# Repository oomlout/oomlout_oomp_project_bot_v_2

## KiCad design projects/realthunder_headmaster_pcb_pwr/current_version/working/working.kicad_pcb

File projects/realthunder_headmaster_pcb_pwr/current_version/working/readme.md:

# headmaster_pcb
 
## summary 
* id: realthunder_headmaster_pcb_pwr
* user: realthunder
* name: headmaster_pcb
* board: pwr
* repo: https://github.com/realthunder/headmaster_pcb
* src_file_repo_kicad_pcb: subs/body/pwr/pwr.kicad_pcb
* src_file_repo_kicad_pcb_link: https://github.com/realthunder/headmaster_pcb/tree/master/subs/body/pwr/pwr.kicad_pcb

* src_file_repo_sch: subs/body/pwr/pwr.sch
* src_file_repo_sch_link: https://github.com/realthunder/headmaster_pcb/tree/master/subs/body/pwr/pwr.sch
* full details link: https://github.com/oomlout/oomlout_oomp_project_bot_v_2/tree/main/projects/realthunder_headmaster_pcb_pwr/current_version/working

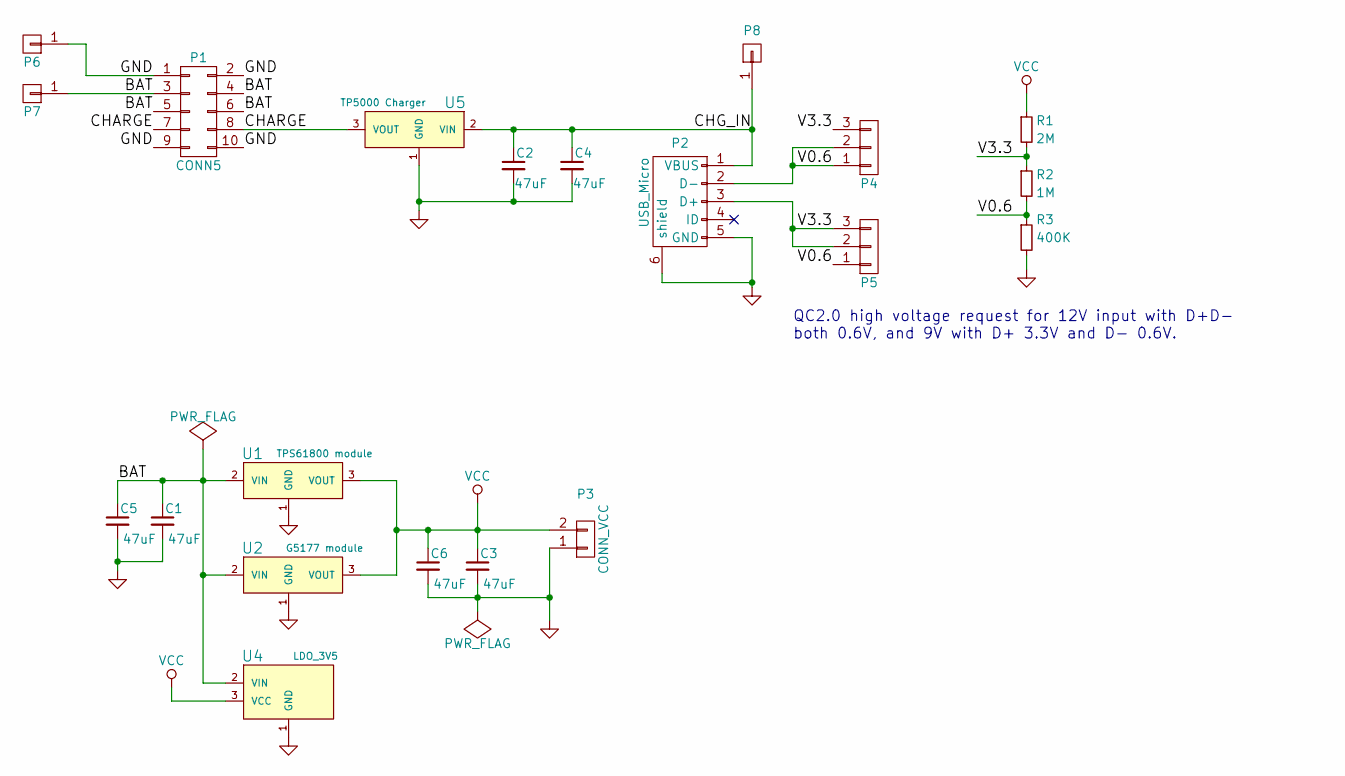
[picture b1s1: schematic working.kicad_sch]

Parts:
C1, C2, C3, C4, C5, C6: 47uF; C_1206
P1: CONN5; Socket_Strip_Straight_2x05
P2: USB_Micro; USB_Micro-B
P3: CONN_VCC; Socket_Strip_Straight_1x02
P4, P5: CONN_01X03; Pin_Header_Straight_1x03_Pitch1.27mm
P6, P7, P8: CONN_01X01; Pin_Header_Straight_1x01
R1: 2M; R_0402
R2: 1M; R_0402
R3: 400K; R_0402
U1: TPS61800 module; DCDC_Conv_TPS61800-Boost
U2: G5177 module; DCDC_Conv_G5177-Boost
U4: LDO_3V5; LDO_RT9018
U5: TP5000 Charger; DCDC_Charger-TP5000-Bucket

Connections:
/BAT: C1.1, C5.1, P1.3, P1.4, P1.5, P1.6, P7.1, U1.2 (VIN), U2.2 (VIN), U4.2 (VIN)
/CHARGE: P1.7, P1.8, U5.3 (VOUT)
/CHG_IN: C2.1, C4.1, P2.1 (VBUS), P8.1, U5.2 (VIN)
/V0.6: P2.2 (D-), P4.1, P4.2, P5.1, R2.2, R3.1
/V3.3: P2.3 (D+), P4.3, P5.2, P5.3, R1.2, R2.1
GND: C1.2, C2.2, C3.2, C4.2, C5.2, C6.2, P1.1, P1.2, P1.9, P1.10, P2.5 (GND), P2.6 (shield), P3.1, P6.1, R3.2, U1.1 (GND), U2.1 (GND), U4.1 (GND), U5.1 (GND)
VCC: C3.1, C6.1, P3.2, R1.1, U1.3 (VOUT), U2.3 (VOUT), U4.3 (VCC)

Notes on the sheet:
QC2.0 high voltage request for 12V input with D+D- both 0.6V, and 9V with D+ 3.3V and D- 0.6V.

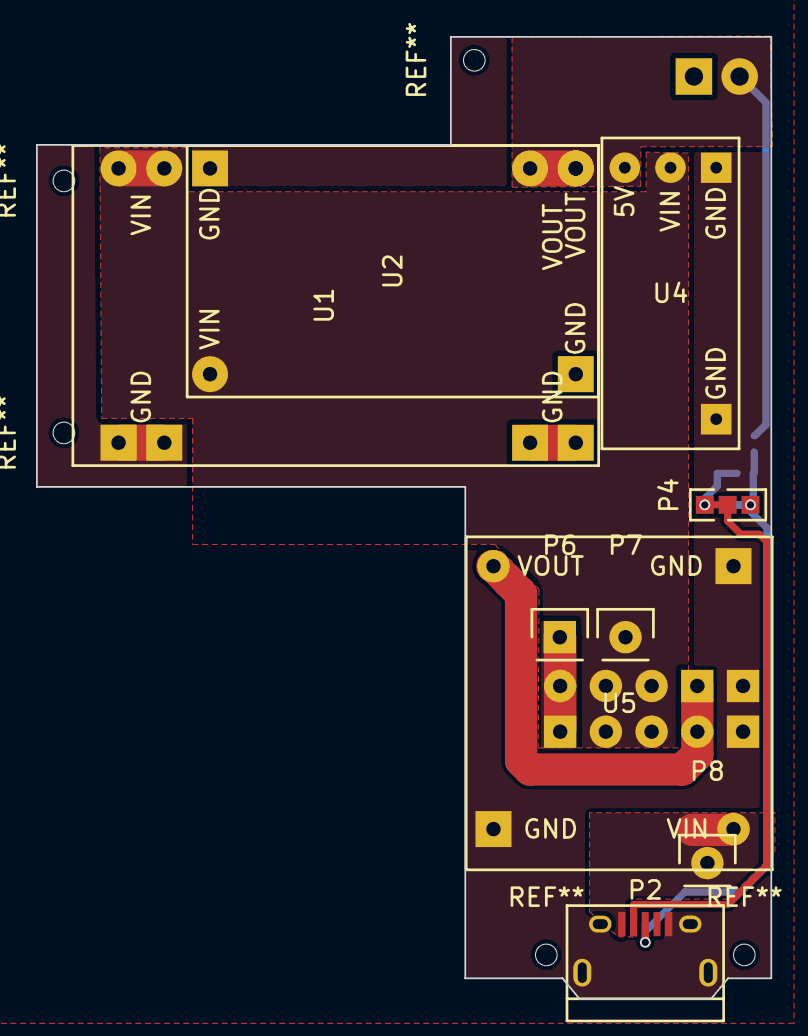
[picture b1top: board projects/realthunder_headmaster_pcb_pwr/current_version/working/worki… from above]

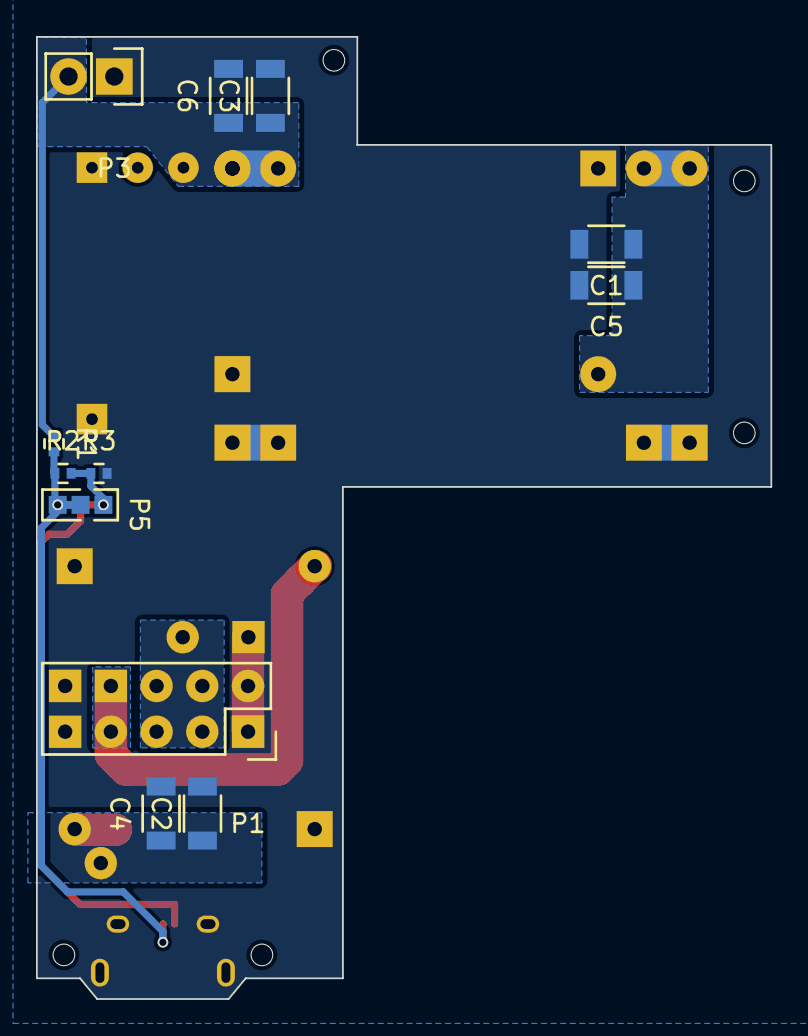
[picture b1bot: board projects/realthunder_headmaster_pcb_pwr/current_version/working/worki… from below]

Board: 2 copper layers, 40.8 x 53.4 mm, 21 parts (12 on the bottom side), 7 nets.

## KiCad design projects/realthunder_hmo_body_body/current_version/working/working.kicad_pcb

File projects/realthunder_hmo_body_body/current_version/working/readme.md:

# hmo_body
 
## summary 
* id: realthunder_hmo_body_body
* user: realthunder
* name: hmo_body
* board: body
* repo: https://github.com/realthunder/hmo_body
* src_file_repo_kicad_pcb: body.kicad_pcb
* src_file_repo_kicad_pcb_link: https://github.com/realthunder/hmo_body/tree/master/body.kicad_pcb

* src_file_repo_sch: body.sch
* src_file_repo_sch_link: https://github.com/realthunder/hmo_body/tree/master/body.sch
* full details link: https://github.com/oomlout/oomlout_oomp_project_bot_v_2/tree/main/projects/realthunder_hmo_body_body/current_version/working

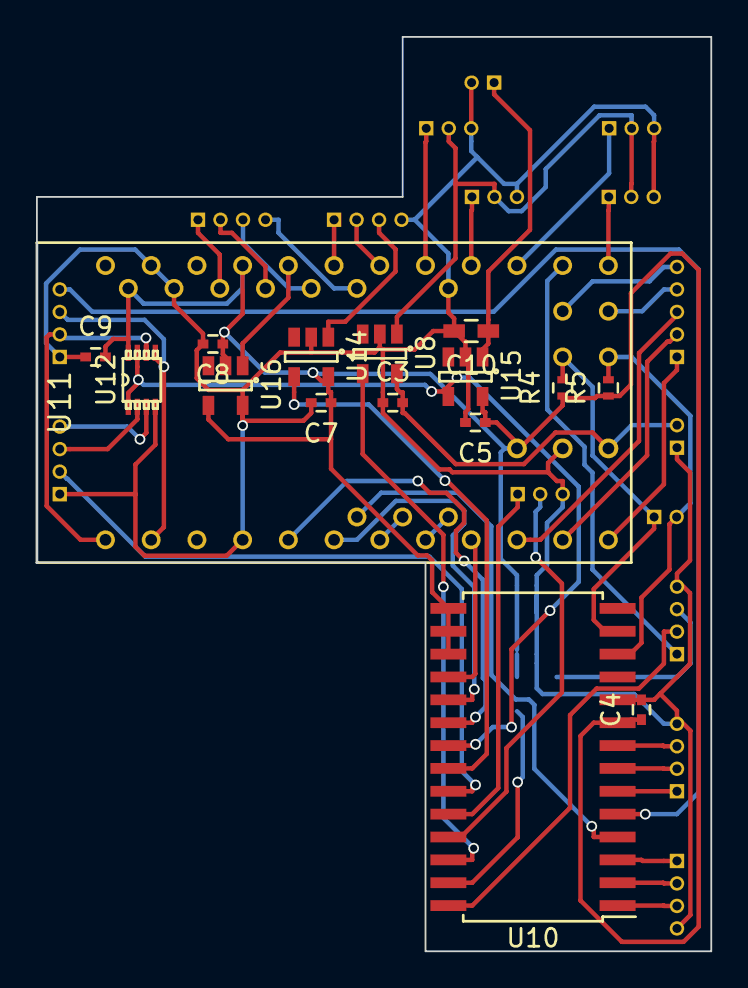
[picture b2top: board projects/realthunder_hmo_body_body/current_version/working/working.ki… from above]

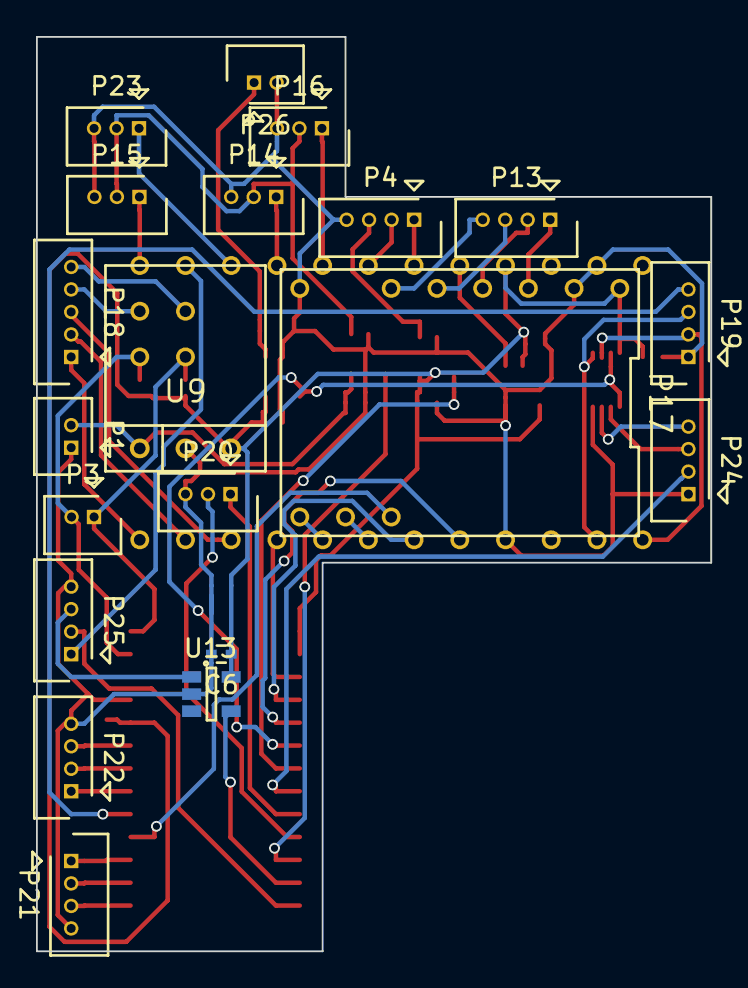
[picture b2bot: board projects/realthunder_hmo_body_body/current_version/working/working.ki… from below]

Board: 2 copper layers, 37.5 x 50.8 mm, 36 parts (20 on the bottom side), 51 nets.

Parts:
C3, C5, C6, C7: 1uF; C_0402
C4, C8, C9: 0.1uF; C_0402
C10: 10uF; C_0603_HandSoldering
P1: CON_VIN; Molex_PicoBlade_53047-0210
P3: CON_I2C; Molex_PicoBlade_53047-0210
P4: CON_LED; Molex_PicoBlade_53047-0410
P13: CON_STEP; Molex_PicoBlade_53047-0410
P14: CON_SRV_CAM; Molex_PicoBlade_53047-0310
P15: CON_SRV_BRAKE; Molex_PicoBlade_53047-0310
P16: CON_SRV_LOCK; Molex_PicoBlade_53047-0310
P17: CON_POLOLU_DRV8834; POLOLU_DRV8834
P18: CON_BAT; Molex_PicoBlade_53047-0510
P19: CON_UART; Molex_PicoBlade_53047-0410
P20: CON_STEP_STOP; Molex_PicoBlade_53047-0310
P21: CON_BTN2; Molex_PicoBlade_53047-0410
P22: CON_BTN1; Molex_PicoBlade_53047-0410
P23: CON_SRV_FOOT; Molex_PicoBlade_53047-0310
P24: CON_EYEPIECE_COM; Molex_PicoBlade_53047-0410
P25: CON_FAN; Molex_PicoBlade_53047-0410
P26: CON_EP_VOUT; Molex_PicoBlade_53047-0210
R4, R5: 10K; R_0402
U8: SRV_SWITCH; SOT-23-5
U9: CON_POLOLU_PWR; POLOLU_U1V10F5
U10: MCP23017; SOIC-28W_7.5x17.9mm_Pitch1.27mm
U11: ProMini; PRO_MINI
U12: 74LVC2G126; TI_DCU_8
U13: FAN_SWITCH; SOT-23-5
U14: LED_SWITCH; SOT-23-5
U15: EP_SWITCH; SOT-23-5
U16: TMP36; SOT-23-5

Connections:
/BAT1_STAT: P18.2, U11.11
/BAT1_VOUT: P18.4, U11.31
/BAT2_STAT: P18.3, U11.10
/BAT2_VOUT: P18.5, U11.32
/BAT_CTL: P18.1, U11.12
/BTN11: P22.1, U10.6
/BTN12: P22.2, U10.7
/BTN13: P22.3, U10.8
/BTN21: P21.1, U10.3
/BTN22: P21.2, U10.2
/BTN23: P21.3, U10.1
/EP_EN: U10.21, U12.1, U12.7, U15.4
/EP_RXD: P24.4, U12.3
/EP_TXD: P24.3, U12.2
/EP_VOUT: C10.1, P26.1, U15.1
/FAN_EN: U10.27, U13.4
/FAN_PWM: P25.1, U11.14
/FAN_TACHO: P25.2, U10.28
/FAN_VOUT: P25.3, U13.1
/FRAME_STOP: P24.2, U10.23
/HOST_INT: P19.4, U10.5
/INTA: U10.20, U11.5
/INTB: U10.19, U11.6
/LED_CLK: P4.1, U11.19
/LED_DAT: P4.2, U11.18
/LED_EN: U10.22, U14.4
/LED_VOUT: P4.3, U14.1
/RXD: P19.3, U11.2, U12.5
/SCL: P3.2, R5.2, U10.12, U11.40
/SDA: P3.1, R4.2, U10.13, U11.39
/SRV_BRAKE: P15.1, U11.13
/SRV_CAM: P14.1, U11.16
/SRV_EN: U8.4, U10.26
/SRV_FOOT: P23.1, U11.15
/SRV_LOCK: P16.1, U11.17
/SRV_VOUT: P14.2, P15.2, P16.2, P23.2, U8.1
/STEP: P17.10, U11.7
/STEP_A1: P13.3, P17.5
/STEP_A2: P13.4, P17.6
/STEP_B1: P13.2, P17.4
/STEP_B2: P13.1, P17.3
/STEP_DIR: P17.9, U11.8
/STEP_STOP1: P20.1, U10.24
/STEP_STOP2: P20.2, U10.25
/TMP: U11.20, U16.1
/TXD: P19.2, U11.1, U12.6
/VIN: C3.2, P1.2, U8.5, U9.1
/~IO_RST: U10.18, U11.9
/~STEP_SLP: P17.11, U10.4
GND: C3.1, C4.2, C5.2, C6.2, C7.2, C8.2, C9.1, C10.2, P1.1, P4.4, P14.3, P15.3, P16.3, P17.2, P17.8, P19.1, P20.3, P21.4, P22.4, P23.3, P24.1, P25.4, P26.2, U8.2, U9.2, U10.10, U11.4, U11.23, U12.4, U13.2, U14.2, U15.2, U16.5
VCC: C4.1, C5.1, C6.1, C7.1, C8.1, C9.2, P17.1, R4.1, R5.1, U9.3, U10.9, U10.15, U10.16, U10.17, U11.21, U12.8, U13.5, U14.5, U15.5, U16.2, U16.4

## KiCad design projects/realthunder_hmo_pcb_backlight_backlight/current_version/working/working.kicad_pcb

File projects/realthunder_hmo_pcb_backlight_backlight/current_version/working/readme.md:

# hmo_pcb_backlight
 
## summary 
* id: realthunder_hmo_pcb_backlight_backlight
* user: realthunder
* name: hmo_pcb_backlight
* board: backlight
* repo: https://github.com/realthunder/hmo_pcb_backlight
* src_file_repo_kicad_pcb: backlight.kicad_pcb
* src_file_repo_kicad_pcb_link: https://github.com/realthunder/hmo_pcb_backlight/tree/master/backlight.kicad_pcb

* src_file_repo_sch: backlight.sch
* src_file_repo_sch_link: https://github.com/realthunder/hmo_pcb_backlight/tree/master/backlight.sch
* full details link: https://github.com/oomlout/oomlout_oomp_project_bot_v_2/tree/main/projects/realthunder_hmo_pcb_backlight_backlight/current_version/working

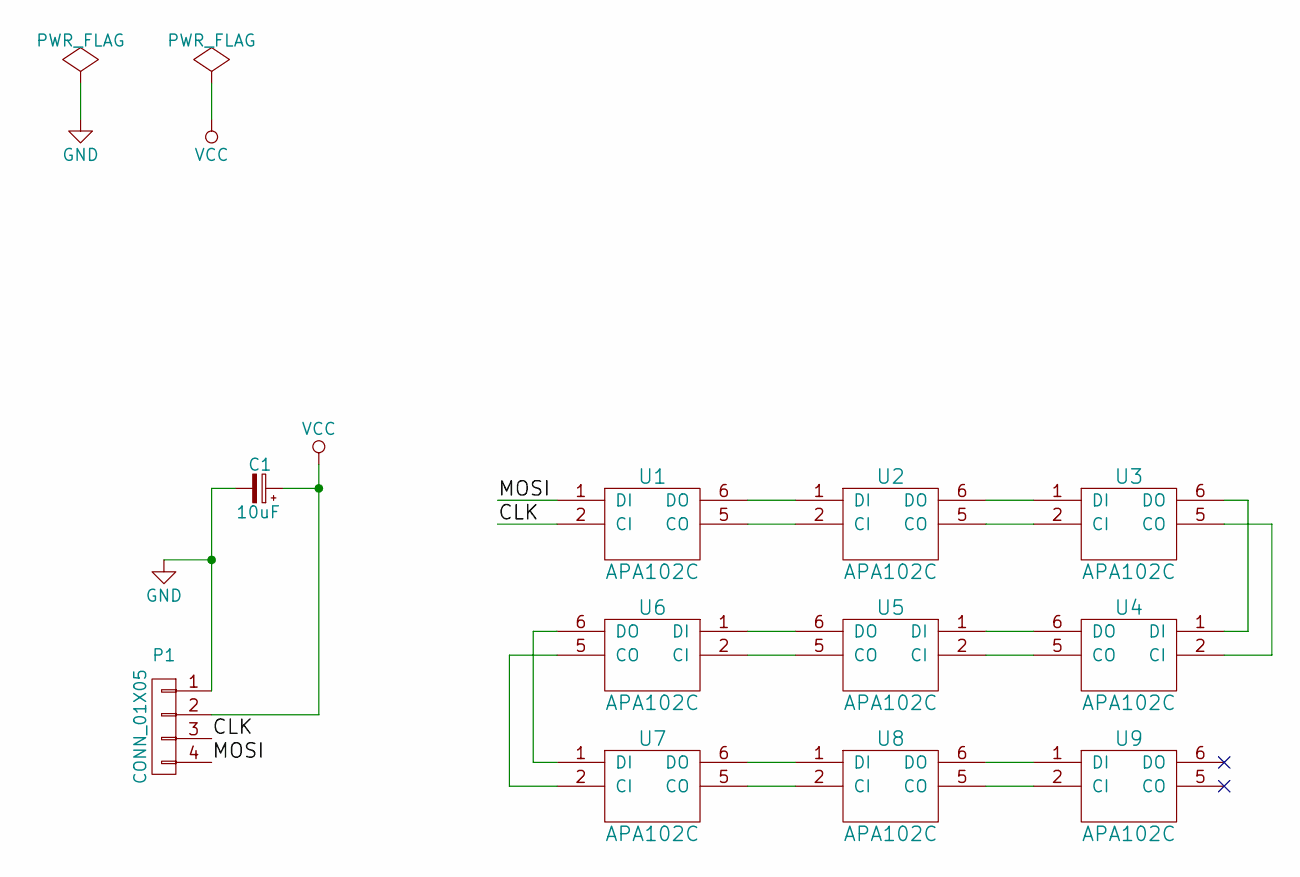
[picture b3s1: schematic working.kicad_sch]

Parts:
C1: 10uF; TantalC_SizeR_EIA-2012
P1: CONN_01X05; Molex_Panelmate-53780-0470_04x1.25mm_Angled
U1, U2, U3, U4, U5, U6, U7, U8, U9: APA102C

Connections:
/CLK: P1.3, U1.2 (CI)
/MOSI: P1.4, U1.1 (DI)
GND: C1.2, P1.1, U1.3 (GND), U2.3 (GND), U3.3 (GND), U4.3 (GND), U5.3 (GND), U6.3 (GND), U7.3 (GND), U8.3 (GND), U9.3 (GND)
unnamed: U1.5 (CO), U2.2 (CI)
unnamed: U1.6 (DO), U2.1 (DI)
unnamed: U2.5 (CO), U3.2 (CI)
unnamed: U2.6 (DO), U3.1 (DI)
unnamed: U3.5 (CO), U4.2 (CI)
unnamed: U3.6 (DO), U4.1 (DI)
unnamed: U4.5 (CO), U5.2 (CI)
unnamed: U4.6 (DO), U5.1 (DI)
unnamed: U5.5 (CO), U6.2 (CI)
unnamed: U5.6 (DO), U6.1 (DI)
unnamed: U6.5 (CO), U7.2 (CI)
unnamed: U6.6 (DO), U7.1 (DI)
unnamed: U7.5 (CO), U8.2 (CI)
unnamed: U7.6 (DO), U8.1 (DI)
unnamed: U8.5 (CO), U9.2 (CI)
unnamed: U8.6 (DO), U9.1 (DI)
VCC: C1.1, P1.2, U1.4 (VCC), U2.4 (VCC), U3.4 (VCC), U4.4 (VCC), U5.4 (VCC), U6.4 (VCC), U7.4 (VCC), U8.4 (VCC), U9.4 (VCC)

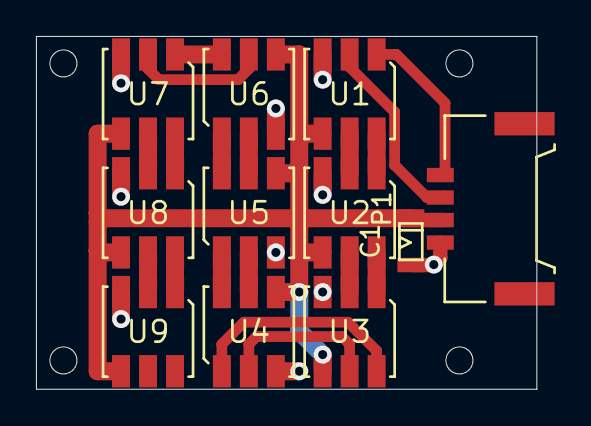
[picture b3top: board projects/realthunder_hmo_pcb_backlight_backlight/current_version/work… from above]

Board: 2 copper layers, 27.8 x 19.6 mm, 11 parts (0 on the bottom side), 20 nets.

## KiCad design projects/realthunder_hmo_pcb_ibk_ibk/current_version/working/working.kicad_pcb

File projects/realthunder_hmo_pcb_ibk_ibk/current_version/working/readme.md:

# hmo_pcb_ibk
 
## summary 
* id: realthunder_hmo_pcb_ibk_ibk
* user: realthunder
* name: hmo_pcb_ibk
* board: ibk
* repo: https://github.com/realthunder/hmo_pcb_ibk
* src_file_repo_kicad_pcb: ibk.kicad_pcb
* src_file_repo_kicad_pcb_link: https://github.com/realthunder/hmo_pcb_ibk/tree/master/ibk.kicad_pcb

* src_file_repo_sch: ibk.sch
* src_file_repo_sch_link: https://github.com/realthunder/hmo_pcb_ibk/tree/master/ibk.sch
* full details link: https://github.com/oomlout/oomlout_oomp_project_bot_v_2/tree/main/projects/realthunder_hmo_pcb_ibk_ibk/current_version/working

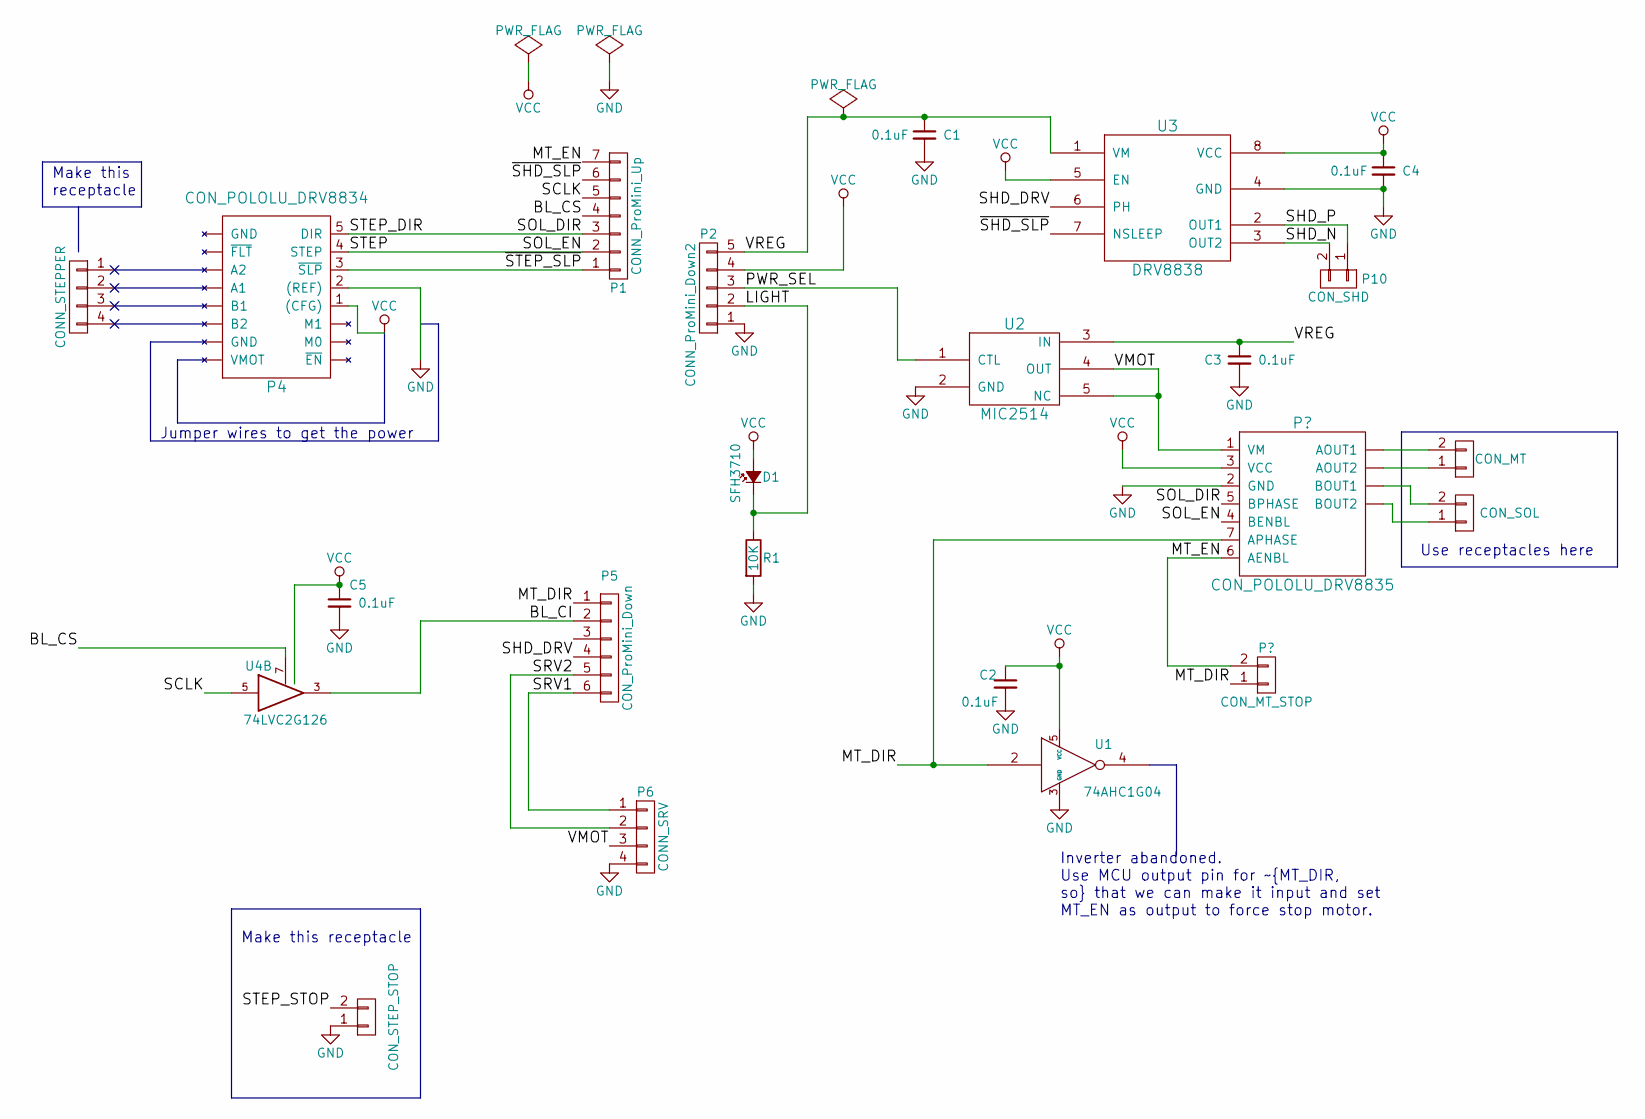
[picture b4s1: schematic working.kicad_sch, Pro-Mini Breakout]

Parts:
C1, C2, C3, C4, C5: 0.1uF; C_0402
D1: SFH3710; LED_0805
P1: CONN_ProMini_Up; Molex_PicoBlade_53261-0771
P2: CONN_ProMini_Down2; Molex_Panelmate-53780-0570_05x1.25mm_Angled
P4: CON_POLOLU_DRV8834; Pin_Header_Straight_1x05
P5: CON_ProMini_Down; Molex_Panelmate-53780-0670_06x1.25mm_Angled
P6: CONN_SRV; Molex_PicoBlade_53048-0410
P10: CON_SHD; Pin_Header_Straight_1x02_Pitch1.27mm
R1: 10K; R_0402
U1: 74AHC1G04; SOT-353
U2: MIC2514; SOT-23-5
U3: DRV8838; DRV8838_DSG_8
U4: 74LVC2G126; SN74LVC2G126_DCU_8

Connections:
/BL_CI: P5.2, U4.3
/BL_CS: P1.4, U4.1, U4.7
/BL_DO: P5.3, U4.2
/LIGHT: D1.1 (K), P2.2, R1.1
/MT_DIR: P5.1, U1.2; also elsewhere on the board
/MT_STOP: P1.7; also elsewhere on the board
/SCLK: P1.5, U4.5
/SHD_DRV: P5.4, U3.6 (PH)
/SHD_N: P10.2, U3.3 (OUT2)
/SHD_P: P10.1, U3.2 (OUT1)
/SOL_DIR: P1.3, P4.5 (DIR)
/SOL_EN: P1.2, P4.4 (STEP)
/SRV1: P5.6, P6.1
/SRV2: P5.5, P6.2
/VMOT: P6.3, U2.4 (OUT), U2.5 (NC); also elsewhere on the board
/VREG: C1.1, C3.1, P2.5, U2.3 (IN), U3.1 (VM)
/~STEP_SLP: P1.1, P4.3 (~SLP), U3.5 (EN)
GND: C1.2, C2.2, C3.2, C4.2, C5.2, P2.1, P4.2 ((REF)), P6.4, R1.2, U1.3 (GND), U2.2 (GND), U3.4 (GND), U3.9, U4.4 (GND); also elsewhere on the board
unnamed 18: U1.4; also elsewhere on the board
VCC: C2.1, C4.1, C5.1, D1.2 (A), P2.4, P4.1 ((CFG)), U1.5 (VCC), U3.8 (VCC), U4.8 (VCC); also elsewhere on the board

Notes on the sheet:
Inverter abandoned. Use MCU output pin for ~{MT_DIR, so} that we can make it input and set MT_EN as output to force stop motor.
Make this receptacle
Jumper wires to get the power
Use receptacles here
Make this receptacle

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
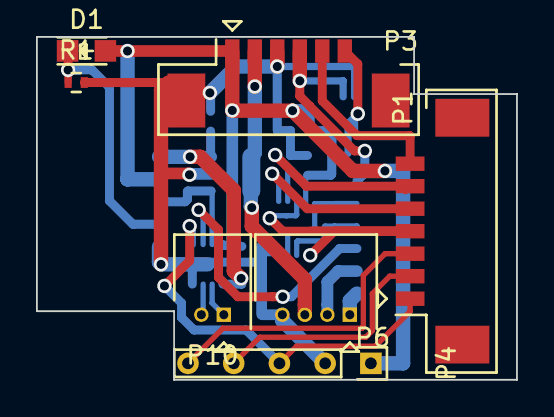
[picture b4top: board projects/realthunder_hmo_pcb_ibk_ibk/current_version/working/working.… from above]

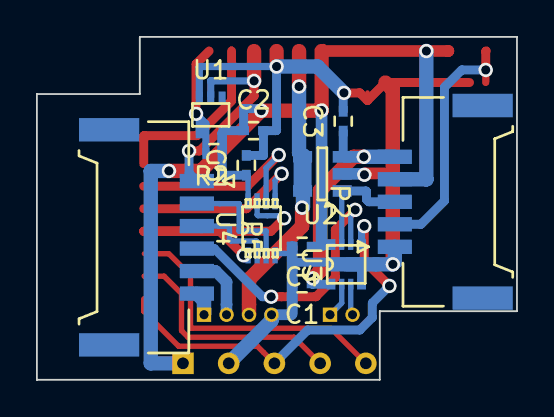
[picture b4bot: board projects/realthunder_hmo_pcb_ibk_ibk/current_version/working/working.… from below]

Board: 2 copper layers, 26.7 x 19.1 mm, 20 parts (13 on the bottom side), 22 nets.

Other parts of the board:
P3: CON_MT; Molex_PicoBlade_53398-0671
R2: 10K; R_0402
__P2: Molex_Panelmate-51146-0500

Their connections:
/MT_DIR: P3.4; also elsewhere on the board
/MT_STOP: P3.5; also elsewhere on the board
/VMOT: P3.2; also elsewhere on the board
GND: P3.3; also elsewhere on the board
unnamed 18: P3.6, R2.2; also elsewhere on the board
VCC: P3.1, R2.1; also elsewhere on the board

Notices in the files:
parts and their libraries:
Copyright 2016 Accelerated Designs. All rights reserved.
